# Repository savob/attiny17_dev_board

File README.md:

# Minimal ATtinyXX17 Board

Barebone ATtiny*XX*17 breakout/development board for the ATtiny417, ATtiny817, ATtiny1617, and ATtiny3217 chips in QFN-24 packaging. All it does is:

- Supply 5V over mini-USB *(if desired, power can also be supplied through edge headers)*
- Provide decoupling capacitors for the chip's supply rail
- Breakout all pins to breadboard-friendly headers
- Provide a standard six-pin AVR-UPDI header

## Possible Improvements

- [ ] Change USB connector to USB-C
- [ ] Add a power LED
- [ ] Add ATtiny-controlled LED(s)

## Software Used

The board files were originally designed in KiCad 6 and ported forward to KiCad 7.0.10.

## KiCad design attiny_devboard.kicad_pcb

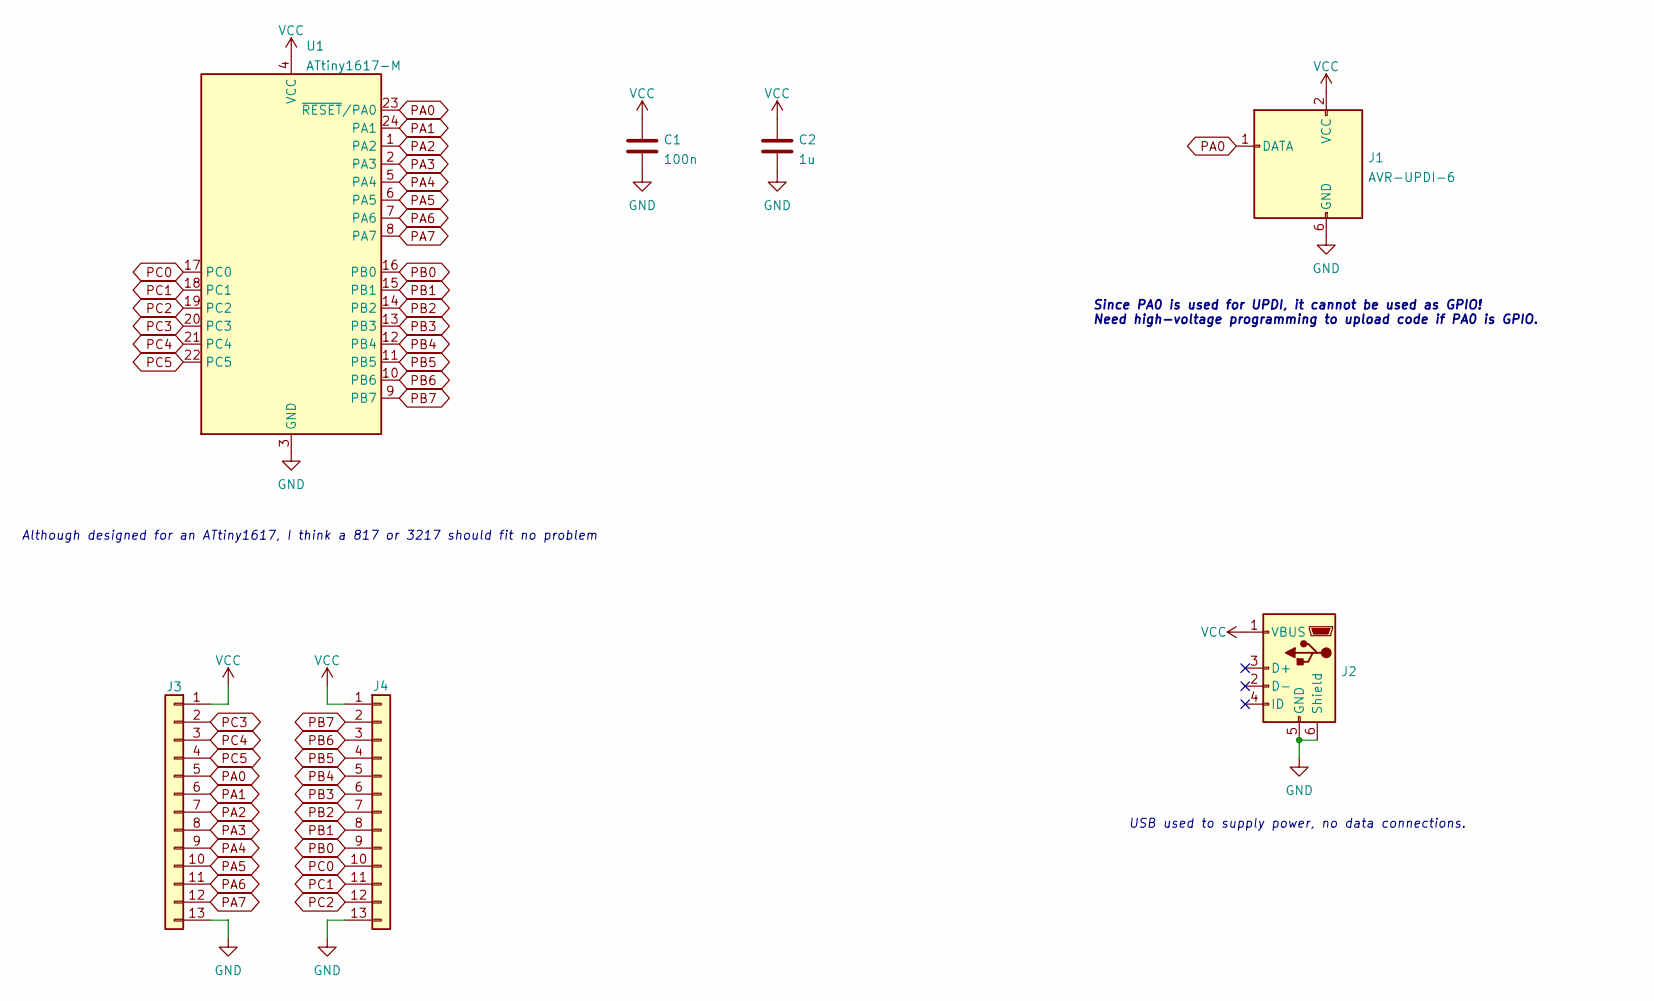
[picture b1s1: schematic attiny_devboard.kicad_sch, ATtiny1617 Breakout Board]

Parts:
C1: 100n; C_0603_1608Metric
C2: 1u; C_0603_1608Metric
J1: AVR-UPDI-6; IDC-Header_2x03_P2.54mm_Vertical
J2: PWR; TE_2172034-1
J3: GPIO1; PinHeader_1x13_P2.54mm_Vertical
J4: GPIO2; PinHeader_1x13_P2.54mm_Vertical
U1: ATtiny1617-M; QFN-24-1EP_4x4mm_P0.5mm_EP2.6x2.6mm

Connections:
GND: C1.2, C2.2, J1.6 (GND), J2.5 (GND), J2.6 (Shield), J3.13, J4.13, U1.3 (GND), U1.25 (GND)
PA0: J1.1 (DATA), J3.5, U1.23 (~RESET/PA0)
PA1: J3.6, U1.24 (PA1)
PA2: J3.7, U1.1 (PA2)
PA3: J3.8, U1.2 (PA3)
PA4: J3.9, U1.5 (PA4)
PA5: J3.10, U1.6 (PA5)
PA6: J3.11, U1.7 (PA6)
PA7: J3.12, U1.8 (PA7)
PB0: J4.9, U1.16 (PB0)
PB1: J4.8, U1.15 (PB1)
PB2: J4.7, U1.14 (PB2)
PB3: J4.6, U1.13 (PB3)
PB4: J4.5, U1.12 (PB4)
PB5: J4.4, U1.11 (PB5)
PB6: J4.3, U1.10 (PB6)
PB7: J4.2, U1.9 (PB7)
PC0: J4.10, U1.17 (PC0)
PC1: J4.11, U1.18 (PC1)
PC2: J4.12, U1.19 (PC2)
PC3: J3.2, U1.20 (PC3)
PC4: J3.3, U1.21 (PC4)
PC5: J3.4, U1.22 (PC5)
VCC: C1.1, C2.1, J1.2 (VCC), J2.1 (VBUS), J3.1, J4.1, U1.4 (VCC)

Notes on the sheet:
Since PA0 is used for UPDI, it cannot be used as GPIO! Need high-voltage programming to upload code if PA0 is GPIO.
USB used to supply power, no data connections.
Although designed for an ATtiny1617, I think a 817 or 3217 should fit no problem

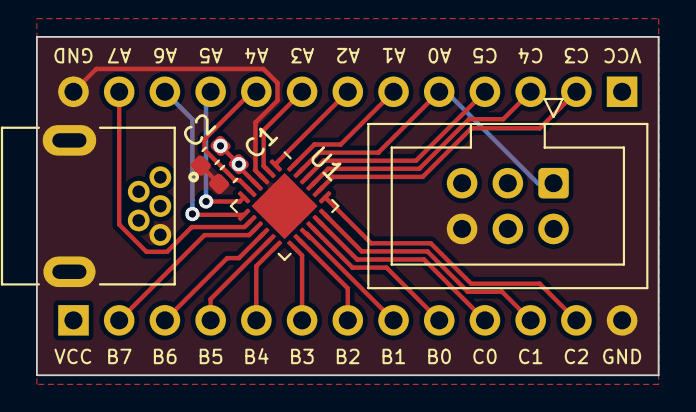
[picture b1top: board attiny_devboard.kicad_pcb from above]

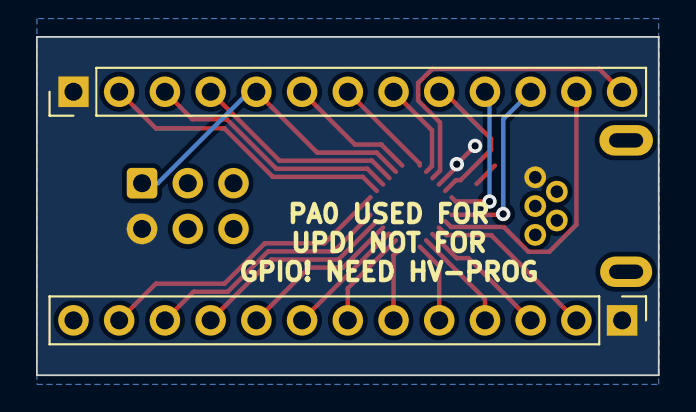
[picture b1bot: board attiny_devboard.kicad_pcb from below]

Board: 2 copper layers, 34.5 x 18.8 mm, 7 parts (2 on the bottom side), 24 nets.

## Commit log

2024-01-04 Uploading hardware files
2024-01-04 Added photo to readme
2024-01-04 Added licence
